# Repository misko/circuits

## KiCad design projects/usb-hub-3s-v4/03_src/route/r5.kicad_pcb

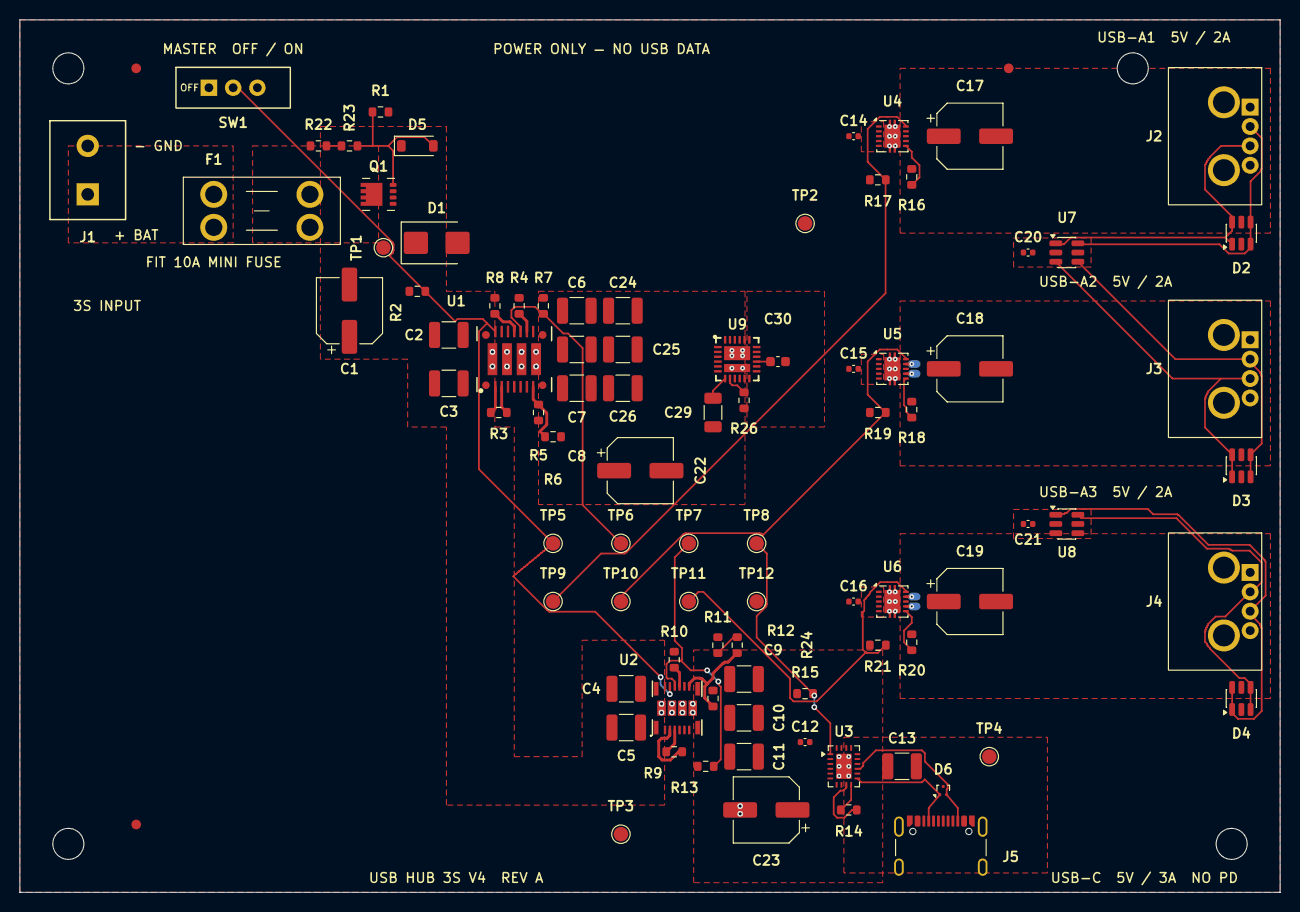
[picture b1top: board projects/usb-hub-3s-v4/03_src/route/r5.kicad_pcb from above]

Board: 4 copper layers, 130.0 x 90.0 mm, 95 parts (0 on the bottom side), 46 nets.

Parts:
C1: C88744; Rubycon_TZV_D6.3x8
C2, C3, C4, C5, C13: 10uF; C_1210_3225Metric
C6, C7, C8, C9, C10, C11, C24, C25, C26: 22uF; C_1210_3225Metric
C12, C14, C15, C16, C20, C21: 100nF; C_0402_1005Metric
C17, C18, C19: C264054; CP_Elec_6.3x5.8
C22: 100uF; CP_Elec_6.3x5.8
C23: 180uF; CP_Elec_6.3x5.8
C29: 47nF; C_1206_3216Metric
C30: 3.3nF; C_0603_1608Metric
D1: C83846; D_SMB
D2, D3, D4: C7519; SOT-23-6
D5: C124196; D_SOD-123
D6: C97502; SOT-9X3
F1: C5249699; Keystone_3568_Mini_Blade_Fuse_Holder
FID1, FID2, FID3: Fiducial_1mm_Mask2mm
H1, H2, H3, H4: MountingHole_3.2mm_M3
J1: C3817933; Phoenix_MKDS_1.5_2_1715022
J2, J3, J4: C5815149; USB_A_GCT_USB1130-15-A_Horizontal
J5: C3020560; GCT_USB4105_GF_A
Q1: C264098; Diodes_PowerDI3333-8_Type_UX
R1, R7, R13, R14, R15, R17, R19, R21, R22, R23: 100kΩ; R_0603_1608Metric
R2: 1MΩ; R_0603_1608Metric
R3, R9: 0Ω; R_0603_1608Metric
R4: 15.8kΩ; R_0603_1608Metric
R5, R11: 41.2kΩ; R_0603_1608Metric
R6, R12: 10kΩ; R_0603_1608Metric
R8: 20kΩ; R_0603_1608Metric
R10: 13kΩ; R_0603_1608Metric
R16, R18, R20: 43.2kΩ; R_0603_1608Metric
R24: 300Ω; R_0603_1608Metric
R26: 210Ω; R_0603_1608Metric
SW1: C273394; E_Switch_EG1218
TP1, TP2, TP3, TP4, TP5, TP6, TP7, TP8, TP9, TP10, TP11, TP12: TP; TestPoint_Pad_D1.5mm
U1: C7125816; Texas_RDF0022A_B3QFN-22_6.5x7.5mm_ThermalVias
U2: C5219289; Texas_RDL0020A_B3QFN-20_5x5.5mm_ThermalVias
U3: C473913; Texas_RVC0020A_WQFN-20-1EP_3x4mm_P0.5mm_EP1.6x2.6mm_Thermal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
U4, U5, U6: C206199; Texas_DRC0010J
U7, U8: C473910; SOT-23-6
U9: C2155765; TI_TPS25982_RGE0024_SplitPad_ThermalVias

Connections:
5VA: C14.1, C15.1, C16.1, C20.1, C21.1, R17.1, R19.1, R21.1, TP2.1, U4.2, U4.3, U4.4, U4.5, U5.2, U5.3, U5.4, U5.5, U6.2, U6.3, U6.4, U6.5, U7.5, U8.5, U9.17, U9.18, U9.19, U9.20, U9.21, U9.22, U9.23, U9.24
5VA_RAW: C6.1, C7.1, C8.1, C22.1, C24.1, C25.1, C26.1, R5.1, R7.1, U1.5, U1.9, U1.10, U9.1, U9.2, U9.3, U9.6, U9.16, U9.25
5VC_RAW: C9.1, C10.1, C11.1, C12.1, C23.1, R11.1, R13.1, R15.1, TP3.1, U2.5, U2.8, U2.9, U3.2, U3.3, U3.4, U3.5, U3.6, U3.7, U3.8
BAT_POS: F1.1, J1.1
BOOT_A_C: R3.2, U1.3
BOOT_A_R: R3.1, U1.2
BOOT_C_C: R9.2, U2.3
BOOT_C_R: R9.1, U2.4
CC1: D6.1, J5.A5, U3.11
CC2: D6.2, J5.B5, U3.13
DM_A1: D2.3, D2.4, J2.2, U7.6
DM_A2: D3.3, D3.4, J3.2, U7.4
DM_A3: D4.3, D4.4, J4.2, U8.6
DP_A1: D2.1, D2.6, J2.3, U7.1
DP_A2: D3.1, D3.6, J3.3, U7.3
DP_A3: D4.1, D4.6, J4.3, U8.1
DVDT_BANK: C30.1, U9.15
EN_BUS: R2.2, SW1.2, TP5.1, U1.17, U2.14
FAULT_A1: R17.2, TP9.1, U4.10
FAULT_A2: R19.2, TP10.1, U5.10
FAULT_A3: R21.2, TP11.1, U6.10
FAULT_C: R15.2, TP8.1, U3.1
FB_A: R5.2, R6.1, U1.8
FB_C: R12.1, R24.2, U2.10
FB_C_TOP: R11.2, R24.1
GND: C1.2, C2.2, C3.2, C4.2, C5.2, C6.2, C7.2, C8.2, C9.2, C10.2, C11.2, C12.2, C13.2, C14.2, C15.2, C16.2, C17.2, C18.2, C19.2, C20.2, C21.2, C22.2, C23.2, C24.2, C25.2, C26.2, C29.2, C30.2, D1.2, D2.2, D3.2, D4.2, D6.3, J1.2, J2.4, J2.SH, J3.4, J3.SH, J4.4, J4.SH, J5.A1, J5.A12, J5.B1, J5.B12, J5.SH, R1.2, R4.2, R6.2, R8.2, R10.2, R12.2, R16.2, R18.2, R20.2, R26.2, SW1.1, TP12.1, U1.7, U1.11, U1.15, U1.19, U1.20, U1.21, U1.22, U2.6, U2.11, U2.17, U2.18, U2.19, U2.20, U3.12, U3.21, U4.1, U4.11, U5.1, U5.11, U6.1, U6.11, U7.2, U8.2, U9.4, U9.5, U9.10, U9.12, U9.14, U9.26
ILIM_A1: R16.1, U4.6
ILIM_A2: R18.1, U5.6
ILIM_A3: R20.1, U6.6
ILIM_BANK: R26.1, U9.8
ITIMER_A: C29.1, U9.7
PG_A: R7.2, TP6.1, U1.13
PG_C: R13.2, TP7.1, U2.13
REF_C: R14.1, U3.10
REF_RTN_C: R14.2, U3.9
RPP_DIV: R22.2, R23.1
RPP_GATE: D5.2, Q1.4, R1.1, R23.2
RT_A: R4.1, U1.12
RT_C: R10.1, U2.12
SPSP_A: R8.1, U1.14
VBAT_FUSED: F1.2, Q1.5, Q1.6, Q1.7, Q1.8
VBUSA1: C17.1, D2.5, J2.1, U4.7, U4.8, U4.9
VBUSA2: C18.1, D3.5, J3.1, U5.7, U5.8, U5.9
VBUSA3: C19.1, D4.5, J4.1, U6.7, U6.8, U6.9
VBUSC: C13.1, J5.A4, J5.A9, J5.B4, J5.B9, TP4.1, U3.14, U3.15
VIN: C1.1, C2.1, C3.1, C4.1, C5.1, D1.1, D5.1, Q1.1, Q1.2, Q1.3, R2.1, R22.1, TP1.1, U1.1, U1.18, U2.1, U2.16

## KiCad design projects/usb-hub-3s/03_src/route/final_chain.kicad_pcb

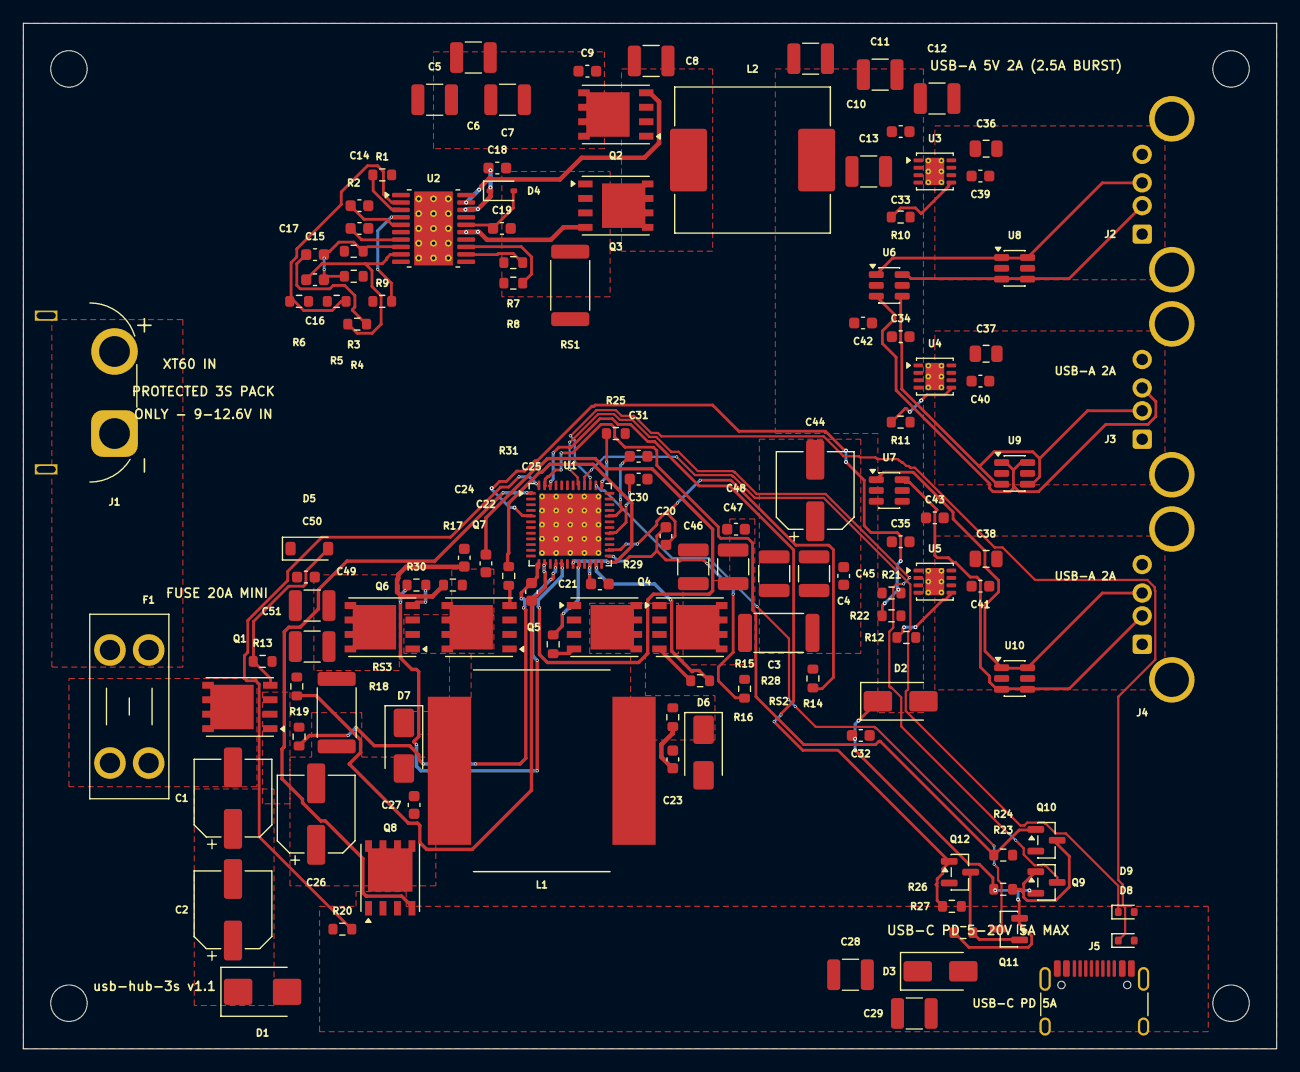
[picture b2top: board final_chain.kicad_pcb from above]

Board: 4 copper layers, 110.0 x 90.0 mm, 128 parts (0 on the bottom side), 71 nets.

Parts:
C1, C2, C44: C2982822; CP_Elec_6.3x7.7
C3, C5, C6, C7, C8, C28, C29, C45, C46, C47, C49, C50: 10uF; C_1210_3225Metric
C4, C9, C21, C22, C27, C33, C34, C35, C39, C40, C41, C42, C43, C48, C51: 100nF; C_0603_1608Metric
C10, C11, C12, C13: 100uF; C_1210_3225Metric
C14: 330pF; C_0603_1608Metric
C15: 3.3nF; C_0603_1608Metric
C16: 100pF; C_0603_1608Metric
C17: 10nF; C_0603_1608Metric
C18, C19, C20, C25, C32: 1uF; C_0603_1608Metric
C23, C24: 1nF; C_0603_1608Metric
C26: C46550465; CP_Elec_6.3x7.7
C30, C31: 2.2uF; C_0603_1608Metric
C36, C37, C38: 22uF; C_0805_2012Metric
D1: C83846; D_SMB
D2: C14996; D_SMA
D3, D7: C148222; D_SMA
D4: C2128; D_SOD-323
D5: C173429; D_SOD-123
D6: C148216; D_SMA
D8, D9: C5246195; D_SOD-523
F1: 3568; Fuseholder_Blade_Mini_Keystone_3568
H1, H2, H3, H4: MountingHole_3.2mm_M3
J1: C98732; XT60PW-M_EdgeTrim
J2, J3, J4: C503996; KH-AF90DIP-112_Horizontal
J5: C5337088; TYPE-C-31-M-12_EdgeTrim
L1: C20613209; L_YJYCOIN_YSPI1770Y
L2: C408523; L_Sunlord_MWSA1206S-6R8
Q1: C2760089; PowerPAK_SO-8_Single
Q2, Q3: C404363; PowerPAK_SO-8_Single
Q4, Q5, Q6, Q7, Q8: C431185; PowerPAK_SO-8_Single
Q9, Q11: C15127; SOT-23
Q10, Q12: C8545; SOT-23
R1: 12.4kΩ; R_0603_1608Metric
R2: 3.74kΩ; R_0603_1608Metric
R3: 1.21kΩ; R_0603_1608Metric
R4: 18kΩ; R_0603_1608Metric
R5: 49.9kΩ; R_0603_1608Metric
R6: 6.98kΩ; R_0603_1608Metric
R7, R8, R25, R28, R29, R30, R31: 0Ω; R_0603_1608Metric
R9, R13: 100kΩ; R_0603_1608Metric
R10, R11, R12: 36.5kΩ; R_0603_1608Metric
R14, R15, R18, R19, R20: 10Ω; R_0603_1608Metric
R16, R17: 2Ω; R_0603_1608Metric
R21, R22, R23, R24, R26, R27: 10kΩ; R_0603_1608Metric
RS1: 10mΩ; R_2512_6332Metric
RS2, RS3: 5mΩ; R_2512_6332Metric
U1: C5140592; QFN-48-1EP_7x7mm_P0.5mm_EP5.45x5.45mm_ThermalVias
U2: C13755; HTSSOP-20-1EP_4.4x6.5mm_P0.65mm_EP3.4x6.5mm_Mask2.75x3.43mm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
U3, U4, U5: C130056; VSON-8-1EP_3x3mm_P0.65mm_EP1.65x2.4mm_ThermalVias
U6, U7: C473910; SOT-23-6
U8, U9, U10: C7519; SOT-23-6

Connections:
5VA: C10.1, C11.1, C12.1, C13.1, C33.1, C34.1, C35.1, C42.1, C43.1, D2.2, L2.2, R2.1, R21.1, U2.10, U3.2, U3.3, U3.4, U4.2, U4.3, U4.4, U5.2, U5.3, U5.4, U6.5, U7.5
BOOT_A: C18.1, D4.1, U2.18
BST1: C22.1, U1.17
BST2: C21.1, U1.22
CC1: J5.A5, Q9.3, U1.41
CC2: J5.B5, Q11.3, U1.38
CMZ_A: C15.1, R4.2
COMP_A: C16.1, R4.1, U2.9
CSF_A: R7.2, U2.12
CSGF_A: R8.2, U2.13
CS_A: Q3.1, Q3.2, Q3.3, R7.1, RS1.1
DMC: D9.1, J5.A7, J5.B7, U1.40
DM_A1: J2.2, U6.6, U8.3, U8.4
DM_A2: J3.2, U6.4, U9.3, U9.4
DM_A3: J4.2, U7.6, U10.3, U10.4
DPC: D8.1, J5.A6, J5.B6, U1.39
DP_A1: J2.3, U6.1, U8.1, U8.6
DP_A2: J3.3, U6.3, U9.1, U9.6
DP_A3: J4.3, U7.1, U10.1, U10.6
EMK1: Q10.1, R24.1, U1.47
EMK2: Q12.1, R27.1, U1.46
EN_A: R9.2, U2.4
EN_PD: R21.2, R22.1, U1.5
FB_A: C15.2, C16.2, R2.2, R3.1, U2.8
GND: C1.2, C2.2, C3.2, C4.2, C5.2, C6.2, C7.2, C8.2, C9.2, C10.2, C11.2, C12.2, C13.2, C14.2, C17.2, C19.2, C23.2, C24.2, C26.2, C27.2, C28.2, C29.2, C30.2, C31.2, C32.2, C33.2, C34.2, C35.2, C36.2, C37.2, C38.2, C39.2, C40.2, C41.2, C42.2, C43.2, C44.2, C45.2, C46.2, C47.2, C48.2, C49.2, C50.2, C51.2, D1.2, D3.2, D6.2, D7.2, D8.2, D9.2, J1.1, J2.4, J2.SH, J3.4, J3.SH, J4.4, J4.SH, J5.A1, J5.A12, J5.B1, J5.B12, J5.SH, Q5.1, Q5.2, Q5.3, Q7.1, Q7.2, Q7.3, Q10.2, Q12.2, R1.2, R3.2, R6.2, R8.1, R10.2, R11.2, R12.2, R13.2, R22.2, R24.2, R25.2, R27.2, RS1.2, U1.11, U1.28, U1.30, U1.49, U2.6, U2.11, U2.14, U2.17, U2.21, U3.1, U3.9, U4.1, U4.9, U5.1, U5.9, U6.2, U7.2, U8.2, U9.2, U10.2
HG1: R30.1, U1.16
HG2: R28.1, U1.23
HO_A: Q2.4, U2.19
ILIM1: R10.1, U3.5
ILIM2: R11.1, U4.5
ILIM3: R12.1, U5.5
LG1: R31.1, U1.19
LG2: R29.1, U1.20
LO_A: Q3.4, U2.15
LX1: C22.2, D7.1, L1.2, Q6.1, Q6.2, Q6.3, Q7.5, R17.1, U1.18
LX2: C21.2, D6.1, L1.1, Q4.1, Q4.2, Q4.3, Q5.5, R16.1, U1.21
PATH_G: Q8.4, U1.1
PDO_CFG: R25.1, U1.37
QG4: Q4.4, R28.2
QG5: Q5.4, R29.2
QG6: Q6.4, R30.2
QG7: Q7.4, R31.2
RAMP_A: C14.1, U2.5
RPP_G: D5.2, Q1.4, R13.1
RT_A: R1.1, U2.3
SNB1: C24.1, R17.2
SNB2: C23.1, R16.2
SNS_IN_N: C20.2, R15.2, U1.25
SNS_IN_P: C20.1, R14.2, U1.26
SNS_OUT_N: C25.2, R19.2, U1.13
SNS_OUT_P: C25.1, R18.2, U1.14
SS_A: C17.1, U2.7
SW_A: C18.2, L2.1, Q2.1, Q2.2, Q2.3, Q3.5, U2.20
UVLO_A: R5.2, R6.1, U2.2
VBAT: F1.1, J1.2
VBAT_F: F1.2, Q1.5
VBUSA1: C36.1, C39.1, J2.1, U3.6, U3.7, U8.5
VBUSA2: C37.1, C40.1, J3.1, U4.6, U4.7, U9.5
VBUSA3: C38.1, C41.1, J4.1, U5.6, U5.7, U10.5
VBUSC: C28.1, C29.1, D3.1, J5.A4, J5.A9, J5.B4, J5.B9, Q8.1, Q8.2, Q8.3, R20.1
VCC5V: C30.1, U1.29
VCCIO: C31.1, U1.32
VCC_A: C19.1, D4.2, U2.16
VCONN5V: C32.1, D2.1, Q9.2, Q11.2, R23.1, R26.1
VCONN_G1: Q9.1, Q10.3, R23.2
VCONN_G2: Q11.1, Q12.3, R26.2
VIN: C1.1, C2.1, C3.1, C4.1, C5.1, C6.1, C7.1, C8.1, C9.1, C44.1, C45.1, D1.1, D5.1, Q1.1, Q1.2, Q1.3, Q2.5, R5.1, R9.1, R14.1, RS2.1, U1.27, U2.1
VIN_S: C46.1, C47.1, C48.1, Q4.5, R15.1, RS2.2, U1.24
VOUT2_SNS: R20.2, U1.48
VOUT_PD: C26.1, C27.1, Q8.5, R19.1, RS3.2, U1.10, U1.12
VOUT_PDS: C49.1, C50.1, C51.1, Q6.5, R18.1, RS3.1, U1.15

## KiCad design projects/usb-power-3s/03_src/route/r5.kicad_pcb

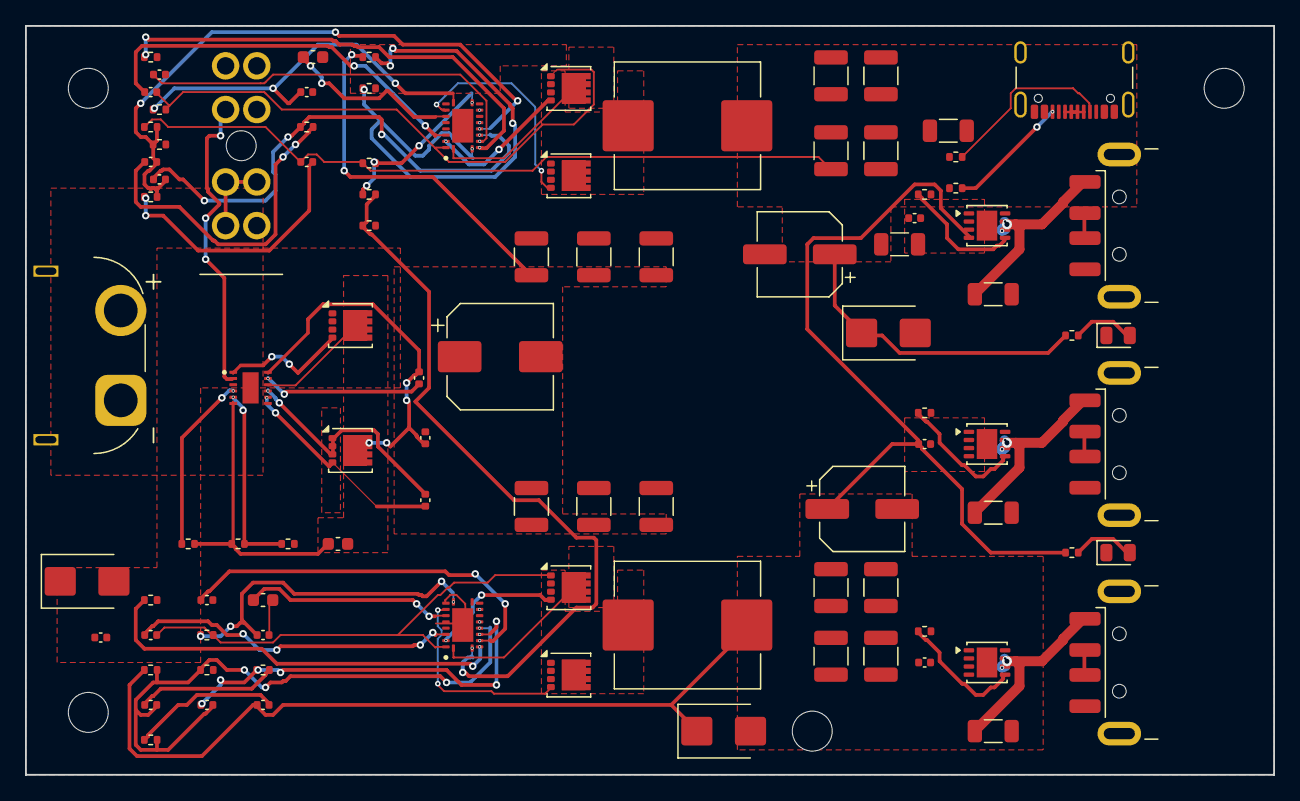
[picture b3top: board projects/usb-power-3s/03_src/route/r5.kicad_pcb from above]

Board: 4 copper layers, 100.0 x 60.0 mm, 100 parts (0 on the bottom side), 54 nets.

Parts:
C1: 100n CAP-VS; C_0402_1005Metric
C2: 100n VS-GND; C_0402_1005Metric
C3: 47n HGATE dv/dt; C_0402_1005Metric
C15: 100n at U1.A; C_0402_1005Metric
C16: 2u2 EN delay; C_0603_1608Metric
C20, C21, C22: 100n sw in; C_0402_1005Metric
C30, C31, C32, C33, C34: 22u port; C_1206_3216Metric
CA1: 47n SS (4ms); C_0402_1005Metric
CA2: 2u2 VCC; C_0603_1608Metric
CA3: 100n BST; C_0402_1005Metric
CA4: 18p CILIM; C_0402_1005Metric
CA7: 220u poly 25mR; CP_Elec_6.3x5.9
CA8: 8n2 CC1; C_0402_1005Metric
CA9: 39p CC2; C_0402_1005Metric
CA10: 1n2 CC3; C_0402_1005Metric
CA51, CA52, CA53: 10u 50V X7R; C_1210_3225Metric
CA61, CA62, CA63, CA64: 47u 10V X7R; C_1210_3225Metric
CB1: 47n SS (4ms); C_0402_1005Metric
CB2: 2u2 VCC; C_0603_1608Metric
CB3: 100n BST; C_0402_1005Metric
CB4: 18p CILIM; C_0402_1005Metric
CB7: 220u poly 25mR; CP_Elec_6.3x5.9
CB8: 8n2 CC1; C_0402_1005Metric
CB9: 39p CC2; C_0402_1005Metric
CB10: 1n2 CC3; C_0402_1005Metric
CB51, CB52, CB53: 10u 50V X7R; C_1210_3225Metric
CB61, CB62, CB63, CB64: 47u 10V X7R; C_1210_3225Metric
CE1: 100u hybrid 35V; CP_Elec_8x10
D1: SMBJ16A; D_SMB
D2, D3: SMBJ5.0A; D_SMB
D4: green 5V_A; LED_0805_2012Metric
D5: green 5V_C; LED_0805_2012Metric
F1: 15A ATO; FuseHolder_ATO_FLR_EdgeTrim
H1, H2, H3, H4: MountingHole_3.2mm_M3
J1: XT60_BATT; XT60PW-M_EdgeTrim
J2, J3, J4: USB-A 2.5A; USB_A_CNCTech_1001-011-01101_Horizontal
J5: USB4105-GF-A; USB_C_Receptacle_GCT_USB4105-xx-A_16P_TopMnt_Horizontal
LA1: MWSA1005S-3R3 16A; L_Sunlord_MWSA1005S
LB1: MWSA1005S-3R3 16A; L_Sunlord_MWSA1005S
Q1: CSD18543Q3A diode; VSON-8_3.3x3.3mm_P0.65mm_NexFET
Q2: CSD18543Q3A switch; VSON-8_3.3x3.3mm_P0.65mm_NexFET
QA1: CSD18543Q3A HS; VSON-8_3.3x3.3mm_P0.65mm_NexFET
QA2: CSD18543Q3A LS; VSON-8_3.3x3.3mm_P0.65mm_NexFET
QB1: CSD18543Q3A HS; VSON-8_3.3x3.3mm_P0.65mm_NexFET
QB2: CSD18543Q3A LS; VSON-8_3.3x3.3mm_P0.65mm_NexFET
R1: 887k ladder-top; R_0402_1005Metric
R2: 52k3 ladder-mid (UVLO 9.33V); R_0402_1005Metric
R3: 82k5 ladder-bot (OV 15.25V); R_0402_1005Metric
R4: 100k EN-A hi (8.5V on); R_0402_1005Metric
R5: 16k5 EN-A lo (7.5V off); R_0402_1005Metric
R16, R17, R18: 24k3 RILIM (2.51A); R_0402_1005Metric
R19: 10k Rp CC1 (3A adv); R_0402_1005Metric
R20: 10k Rp CC2 (3A adv); R_0402_1005Metric
R21: 20k PGOOD_A pu (5V_C); R_0402_1005Metric
R22: 1k LED-A; R_0402_1005Metric
R23: 1k LED-C; R_0402_1005Metric
R33: 20k seq div hi; R_0402_1005Metric
R34: 16k5 seq div lo; R_0402_1005Metric
RA1: 16k5 RT (606kHz); R_0402_1005Metric
RA2: 348R RILIM (wc 6.3A); R_0402_1005Metric
RA3: 20k RFB1; R_0402_1005Metric
RA4: 3k74 RFB2 (5.08V); R_0402_1005Metric
RA5: 13k RC1; R_0402_1005Metric
RA6: 4k64 RC2; R_0402_1005Metric
RB1: 16k5 RT (606kHz); R_0402_1005Metric
RB2: 432R RILIM (wc 7.8A); R_0402_1005Metric
RB3: 20k RFB1; R_0402_1005Metric
RB4: 3k74 RFB2 (5.08V); R_0402_1005Metric
RB5: 13k RC1; R_0402_1005Metric
RB6: 4k64 RC2; R_0402_1005Metric
U1: LM74800-Q1; WSON-12_3x3_P0.5_LM74800DRR
U2: LM5145 rail A; VQFN-20_3.5x4.5_P0.5_LM5145RGY
U3: LM5145 rail B; VQFN-20_3.5x4.5_P0.5_LM5145RGY
U4, U5, U6: TPS2557 2.5A; VSON-8-1EP_3x3mm_P0.65mm_EP1.65x2.4mm

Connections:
5V_A: C20.1, C21.1, C22.1, CB7.1, CB10.1, CB61.1, CB62.1, CB63.1, CB64.1, D2.1, LB1.2, R22.1, RB3.1, U4.2, U4.3, U4.4, U5.2, U5.3, U5.4, U6.2, U6.3, U6.4
5V_C: C33.1, C34.1, CA7.1, CA10.1, CA61.1, CA62.1, CA63.1, CA64.1, D3.1, J5.A4, J5.A9, J5.B4, J5.B9, LA1.2, R19.1, R20.1, R21.1, R23.1, RA3.1
BST_A: CA3.1, U2.17
BST_B: CB3.1, U3.17
CC1: J5.A5, R19.2
CC2: J5.B5, R20.2
COMP_A: CA9.1, RA5.1, U2.4
COMP_B: CB9.1, RB5.1, U3.4
CX_A: CA8.1, RA5.2
CX_B: CB8.1, RB5.2
CY_A: CA10.2, RA6.1
CY_B: CB10.2, RB6.1
DCP1: J2.2, J2.3
DCP2: J3.2, J3.3
DCP3: J4.2, J4.3
DCPC: J5.A6, J5.A7, J5.B6, J5.B7
DG_FE: Q1.4, U1.1
EN_A: R4.2, R5.1, U2.1
FB_A: CA8.2, CA9.2, RA3.2, RA4.1, RA6.2, U2.5
FB_B: CB8.2, CB9.2, RB3.2, RB4.1, RB6.2, U3.5
FE_CAP: C1.1, U1.11
FE_EN: C16.1, R1.2, R2.1, U1.6
FE_LAD: R1.1, U1.4
FE_MID: C1.2, C2.1, Q1.5, Q2.5, U1.10, U1.12
FE_OV: R2.2, R3.1, U1.5
GND: C2.2, C15.2, C16.2, C20.2, C21.2, C22.2, C30.2, C31.2, C32.2, C33.2, C34.2, CA1.2, CA2.2, CA4.2, CA7.2, CA51.2, CA52.2, CA53.2, CA61.2, CA62.2, CA63.2, CA64.2, CB1.2, CB2.2, CB4.2, CB7.2, CB51.2, CB52.2, CB53.2, CB61.2, CB62.2, CB63.2, CB64.2, CE1.2, D1.2, D2.2, D3.2, D4.1, D5.1, J1.1, J2.4, J2.SH, J3.4, J3.SH, J4.4, J4.SH, J5.A1, J5.A12, J5.B1, J5.B12, J5.SH, QA2.1, QA2.2, QA2.3, QB2.1, QB2.2, QB2.3, R3.2, R5.2, R16.2, R17.2, R18.2, R34.2, RA1.2, RA4.2, RB1.2, RB4.2, U1.7, U2.6, U2.8, U2.12, U2.21, U3.6, U3.8, U3.12, U3.21, U4.1, U4.9, U5.1, U5.9, U6.1, U6.9
HG_FE: C3.1, Q2.4, U1.8
HO_A: QA1.4, U2.18
HO_B: QB1.4, U3.18
ILIM1: R16.1, U4.5
ILIM2: R17.1, U5.5
ILIM3: R18.1, U6.5
ILIM_A: CA4.1, RA2.1, U2.11
ILIM_B: CB4.1, RB2.1, U3.11
LEDA_A: D4.2, R22.2
LEDC_A: D5.2, R23.2
LO_A: QA2.4, U2.13
LO_B: QB2.4, U3.13
PGOODA_RAW: R21.2, R33.1, U2.10
PGOOD_A: R33.2, R34.1, U3.1
RT_A: RA1.1, U2.2
RT_B: RB1.1, U3.2
SS_A: CA1.1, U2.3
SS_B: CB1.1, U3.3
SW_A: CA3.2, LA1.1, QA1.1, QA1.2, QA1.3, QA2.5, RA2.2, U2.19
SW_B: CB3.2, LB1.1, QB1.1, QB1.2, QB1.3, QB2.5, RB2.2, U3.19
VBATT_F: C15.1, D1.1, F1.2, Q1.1, Q1.2, Q1.3, U1.2, U1.3
VBATT_RAW: F1.1, J1.2
VBUS1: C30.1, J2.1, U4.6, U4.7
VBUS2: C31.1, J3.1, U5.6, U5.7
VBUS3: C32.1, J4.1, U6.6, U6.7
VCC_A: CA2.1, U2.14
VCC_B: CB2.1, U3.14
VSW: C3.2, CA51.1, CA52.1, CA53.1, CB51.1, CB52.1, CB53.1, CE1.1, Q2.1, Q2.2, Q2.3, QA1.5, QB1.5, R4.1, U1.9, U2.20, U3.20
